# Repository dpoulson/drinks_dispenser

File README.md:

drinks_dispenser
================

Schematics, code, and laser cutting files for my drinks dispenser

Laser cutting files can be found in the Chassis folder

Circuit schematics, and board layouts, can be found in the EagleCad directory

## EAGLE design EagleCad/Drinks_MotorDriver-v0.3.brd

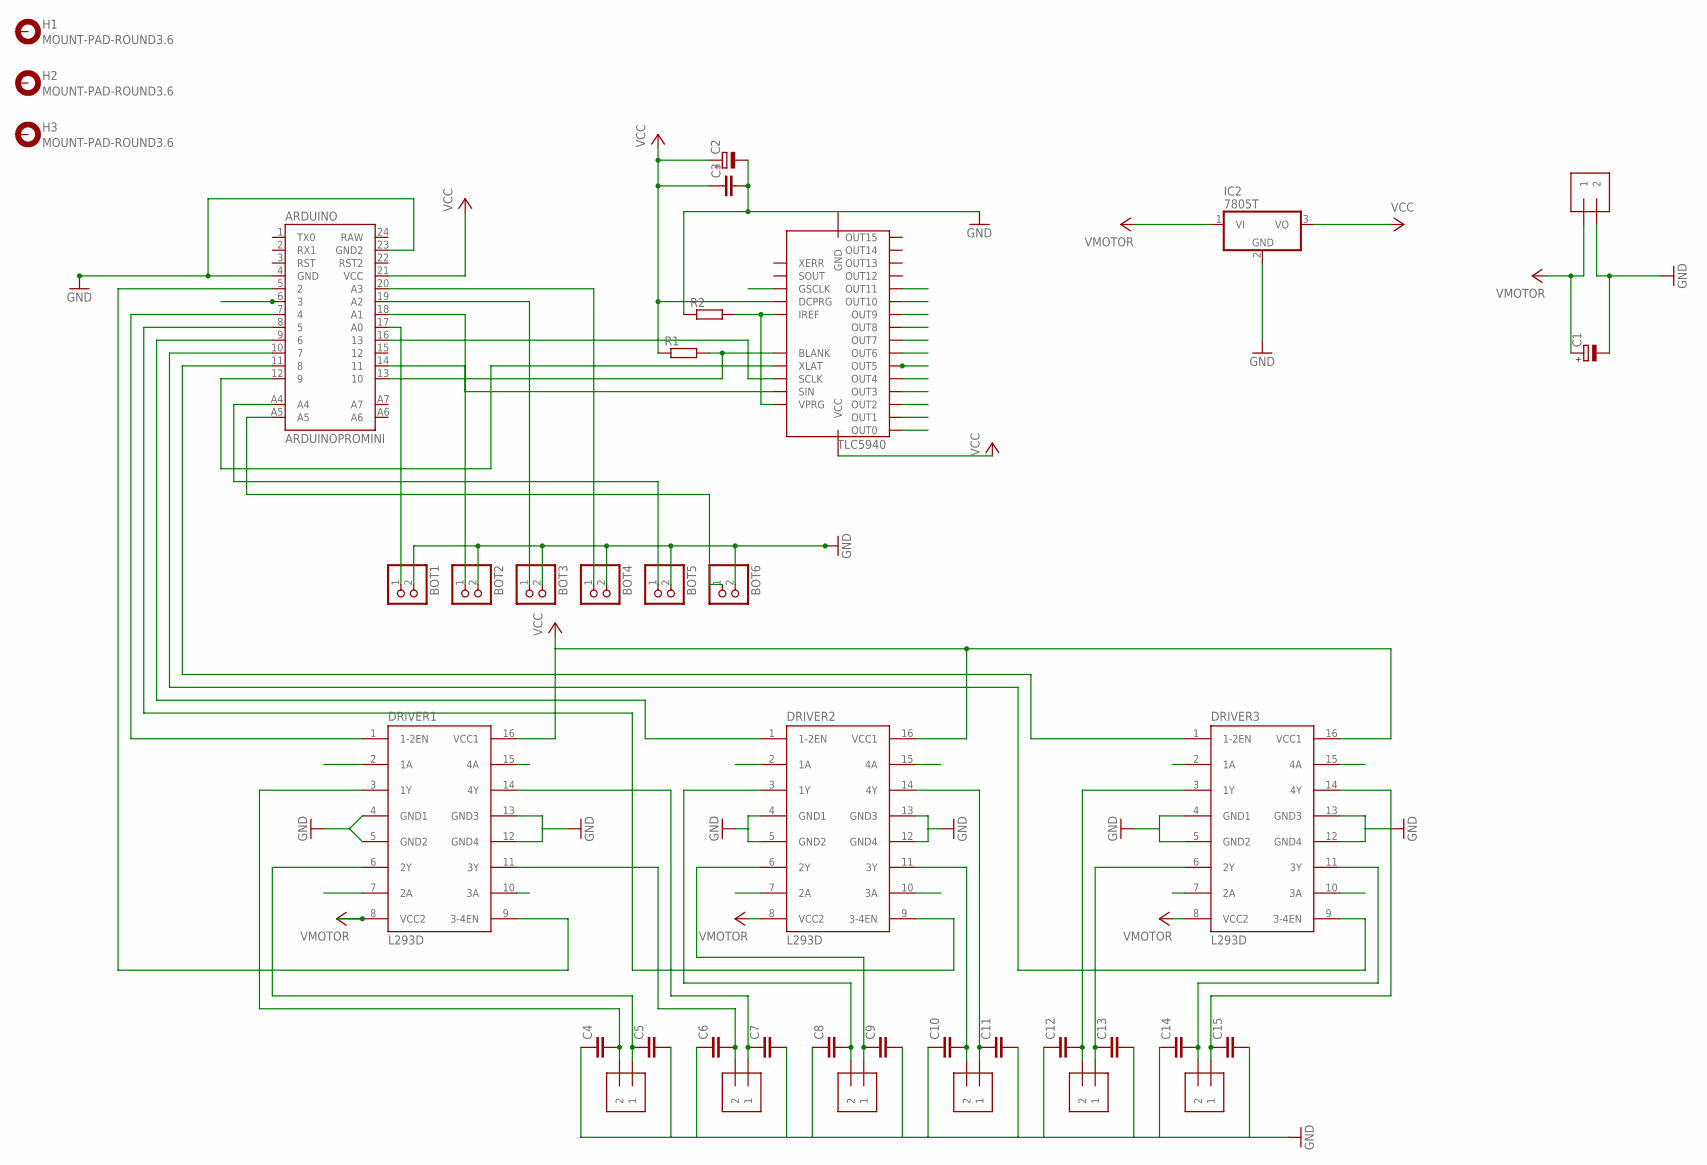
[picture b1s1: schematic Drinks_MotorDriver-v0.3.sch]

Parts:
ARDUINO: ARDUINOPROMINI; ARDUINO_PRO_MINI
BOT1, BOT2, BOT3, BOT4, BOT5, BOT6: JST_2PIN-THM; JST-PH-2-THM
C1, C2: CPOL-EUE5-8.5; E5-8,5
C3, C4, C5, C6, C7, C8, C9, C10, C11, C12, C13, C14, C15: C-EU025-025X050; C025-025X050
DRIVER1, DRIVER2, DRIVER3: L293D; DIL16
H1, H2, H3: MOUNT-PAD-ROUND3.6; 3,6-PAD
IC2: 7805T; TO220H
MOT1, MOT2, MOT3, MOT4, MOT5, MOT6: 1X2-3.5MM
R1, R2: R-EU_0204/7; 0204/7
TLC5940: IC-PACKAGE_DIL28-4
VIN: 1X2-3.5MM

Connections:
GND: ARDUINO.4 (GND), ARDUINO.23 (GND2), BOT1.2 (1), BOT2.2 (1), BOT3.2 (1), BOT4.2 (1), BOT5.2 (1), BOT6.2 (1), C1.-, C2.-, C3.2, C4.1, C5.2, C6.1, C7.2, C8.1, C9.2, C10.1, C11.2, C12.1, C13.2, C14.1, C15.2, DRIVER1.4 (GND1), DRIVER1.5 (GND2), DRIVER1.12 (GND4), DRIVER1.13 (GND3), DRIVER2.4 (GND1), DRIVER2.5 (GND2), DRIVER2.12 (GND4), DRIVER2.13 (GND3), DRIVER3.4 (GND1), DRIVER3.5 (GND2), DRIVER3.12 (GND4), DRIVER3.13 (GND3), IC2.2 (GND), R2.1, TLC5940.22 (GND), VIN.2
GSCLK: ARDUINO.6 (3), TLC5940.18 (GSCLK)
MOT1A: DRIVER1.2 (1A), TLC5940.28 (OUT0)
MOT1B: DRIVER1.7 (2A), TLC5940.1 (OUT1)
MOT2A: DRIVER1.10 (3A), TLC5940.2 (OUT2)
MOT2B: DRIVER1.15 (4A), TLC5940.3 (OUT3)
MOT3A: DRIVER2.2 (1A), TLC5940.4 (OUT4)
MOT3B: DRIVER2.7 (2A), TLC5940.5 (OUT5)
MOT4A: DRIVER2.10 (3A), TLC5940.6 (OUT6)
MOT4B: DRIVER2.15 (4A), TLC5940.7 (OUT7)
MOT5A: DRIVER3.2 (1A), TLC5940.8 (OUT8)
MOT5B: DRIVER3.7 (2A), TLC5940.9 (OUT9)
MOT6A: DRIVER3.10 (3A), TLC5940.10 (OUT10)
MOT6B: DRIVER3.15 (4A), TLC5940.11 (OUT11)
unnamed: ARDUINO.13 (10), R1.2, TLC5940.23 (BLANK)
unnamed: R2.2, TLC5940.20 (IREF), TLC5940.27 (VPRG)
unnamed: ARDUINO.14 (11), TLC5940.26 (SIN)
unnamed: ARDUINO.17 (A0), BOT1.1 (2)
unnamed: ARDUINO.12 (9), TLC5940.24 (XLAT)
unnamed: ARDUINO.18 (A1), BOT2.1 (2)
unnamed: ARDUINO.19 (A2), BOT3.1 (2)
unnamed: ARDUINO.20 (A3), BOT4.1 (2)
unnamed: ARDUINO.A4, BOT5.1 (2)
unnamed: ARDUINO.5 (2), DRIVER1.9 (3-4EN)
unnamed: ARDUINO.7 (4), DRIVER1.1 (1-2EN)
unnamed: ARDUINO.8 (5), DRIVER2.9 (3-4EN)
unnamed: ARDUINO.A5, BOT6.1 (2)
unnamed: ARDUINO.9 (6), DRIVER2.1 (1-2EN)
unnamed: ARDUINO.10 (7), DRIVER3.9 (3-4EN)
unnamed: ARDUINO.11 (8), DRIVER3.1 (1-2EN)
unnamed: C4.2, DRIVER1.3 (1Y), MOT1.2
unnamed: C5.1, DRIVER1.6 (2Y), MOT1.1
unnamed: C7.1, DRIVER1.14 (4Y), MOT2.1
unnamed: C6.2, DRIVER1.11 (3Y), MOT2.2
unnamed: C8.2, DRIVER2.3 (1Y), MOT3.2
unnamed: C9.1, DRIVER2.6 (2Y), MOT3.1
unnamed: C10.2, DRIVER2.11 (3Y), MOT4.2
unnamed: C11.1, DRIVER2.14 (4Y), MOT4.1
unnamed: C12.2, DRIVER3.3 (1Y), MOT5.2
unnamed: C13.1, DRIVER3.6 (2Y), MOT5.1
unnamed: C14.2, DRIVER3.11 (3Y), MOT6.2
unnamed: C15.1, DRIVER3.14 (4Y), MOT6.1
SCLK: ARDUINO.16 (13), TLC5940.25 (SCLK)
VCC: ARDUINO.21 (VCC), C2.+, C3.1, DRIVER1.16 (VCC1), DRIVER2.16 (VCC1), DRIVER3.16 (VCC1), IC2.3 (VO), R1.1, TLC5940.19 (DCPRG), TLC5940.21 (VCC)
VMOTOR: C1.+, DRIVER1.8 (VCC2), DRIVER2.8 (VCC2), DRIVER3.8 (VCC2), IC2.1 (VI), VIN.1

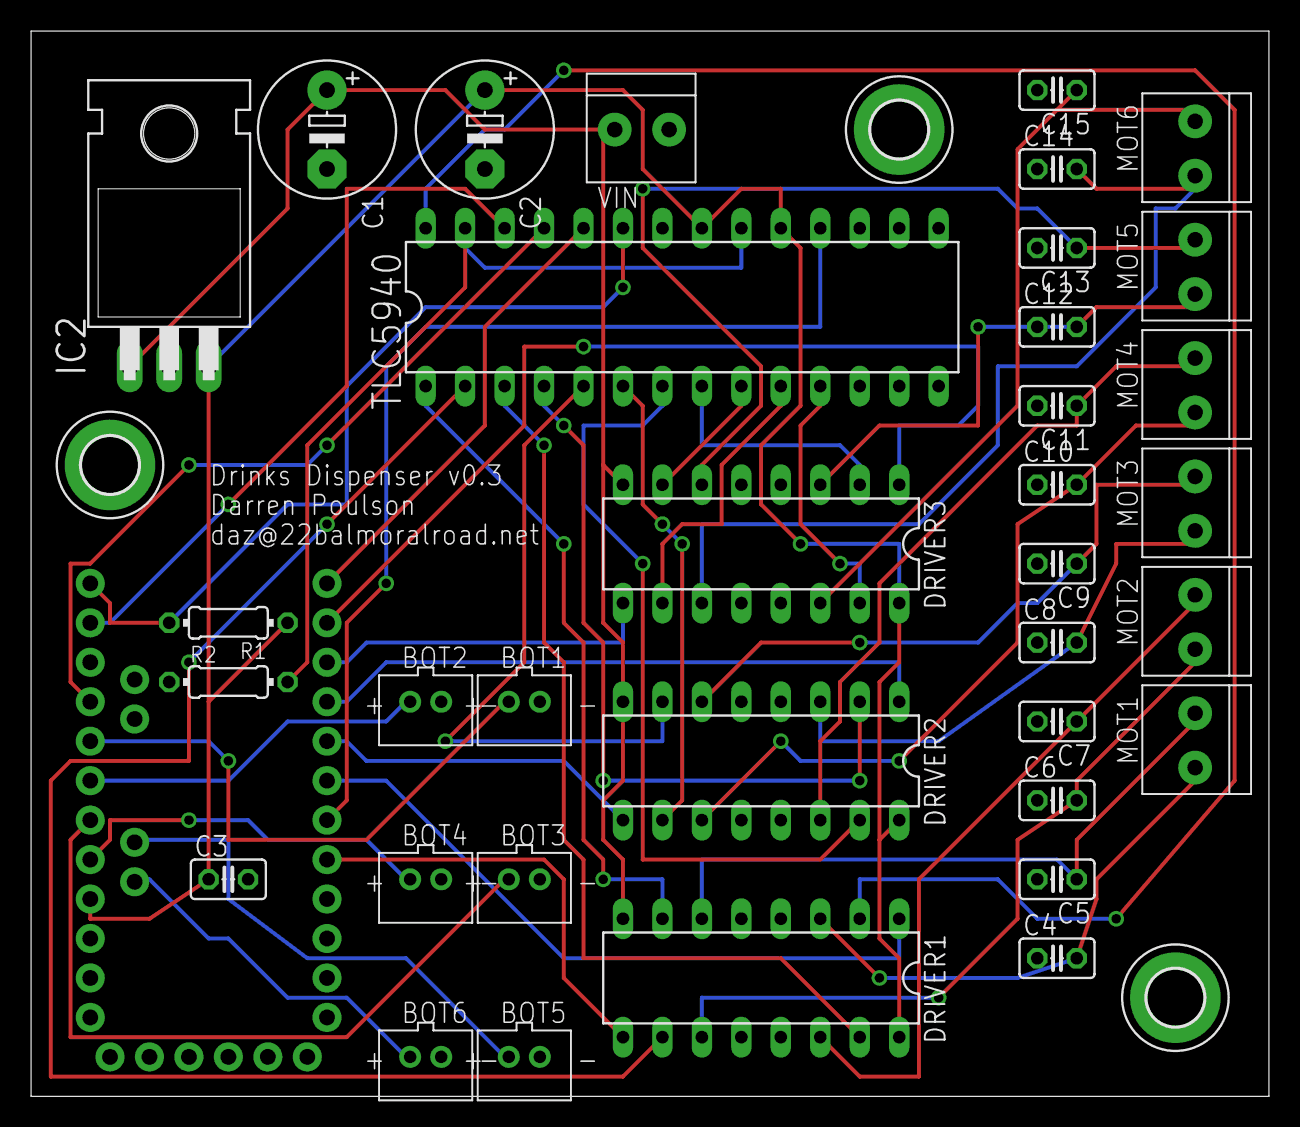
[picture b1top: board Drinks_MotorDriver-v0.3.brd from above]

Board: 2 copper layers, 79.7 x 68.6 mm, 39 parts (0 on the bottom side), 45 nets.

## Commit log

2014-02-20 Added the laser cutting files
2014-02-20 Added EagleCad files
2017-11-26 KiCAD schematics and start on interface
2017-11-26 Added initial script for turning motors on
2017-11-27 Now puts out 16 bits to MCP23017
2017-11-27 Some tweaks...

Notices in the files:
parts and their libraries:
SparkFun-Boards: Licensing: CC v3.0 Share-Alike You are welcome to use this library for commercial purposes.
